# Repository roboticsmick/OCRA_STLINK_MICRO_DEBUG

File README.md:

# ORCA STLINK micro debug tool

Ultra small and low cost STM debugger PCB footprint and programmer PCB. 

## PCB footprint for Fusion 360 

The footprint uses an offset design to ensure you can't connected in reverse. The end pads are through hole pads to act as registration points that the pogo pins align too to keep the profile as small as possible. 

## Programmer PCB boards and Peg

You can find the peg for programming of Aliexpress. This comes disassembled, so you can easily replace the board with the ORCA STLINK micro debug tool PCBs and then connect to your STLINK debugger to program your board.

You will also need to buy a header for your STLINK programmer. This is a 14 pin header, with a 1.27mm pitch. I used one like this:

Alterantively, I've broken our all the STLINK header pins with large 1mm header pins, so you can connect using easily sources 2.54mm header pins, or you can directly solder wires to the pads.

## PCB Design guide instructions

1. Make sure the pads are accessible with the programmer on your PCB design. The component should be near the side of your board, so it can be easily clipped. Ideally make sure no PCB parts obstruct the clip as it's moved into place, as your pogo pins on the programmer could scratch against the components on the board. Always have the peg open all the way when placing the programmer, so the pogo pins do not scratch the PCB.

2. You also need to consider the opposite side of the PCB, as the peg will press against this side of the board to hold the programmer in place. Don't place fragile parts in either areas to prevent damage.

## Programming and debugging

I use a STLINK-V3MINIE. These cost ~$20AU from Digikey to purchase. They incredible value, and make programming with STM32 chips really easy using Zephyr RTOS or Arduino.

## Send some love if you found this helpful

This is completely open source to help out other engineers and tinkers. Enjoy :heart:

If you found it useful though and making bank, feel free to send me some coffees so I can keep making stuff open source!

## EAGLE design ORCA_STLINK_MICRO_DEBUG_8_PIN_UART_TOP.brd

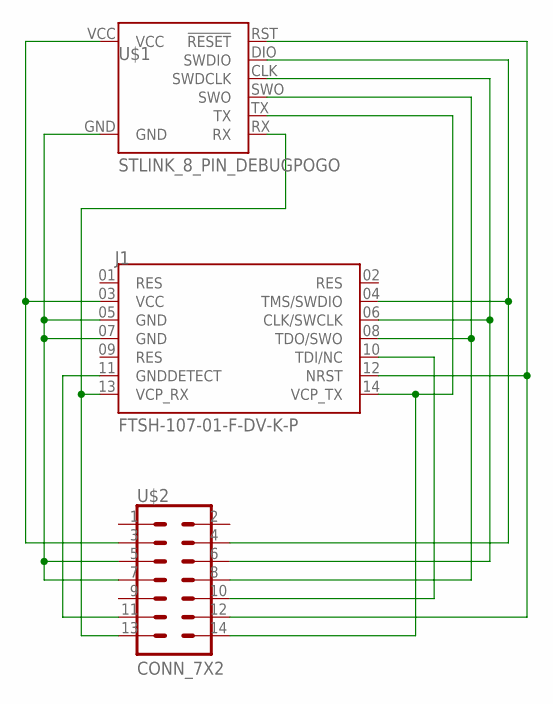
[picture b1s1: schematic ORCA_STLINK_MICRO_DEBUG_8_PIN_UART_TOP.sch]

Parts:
J1: FTSH-107-01-F-DV-K-P; SAMTEC_FTSH-107-01-F-DV-K-P
U$1: STLINK_8_PIN_DEBUGPOGO; STLINK_8_PIN_POGO
U$2: CONN_7X2; 2X07

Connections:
!RST: J1.12 (NRST), U$1.RST (!RESET), U$2.12
CLK: J1.06 (CLK/SWCLK), U$1.CLK (SWDCLK), U$2.6
DIO: J1.04 (TMS/SWDIO), U$1.DIO (SWDIO), U$2.4
GND: J1.05 (GND), J1.07 (GND), U$1.GND, U$2.5, U$2.7
GND_DETECT: J1.11 (GNDDETECT), U$2.11
SWO: J1.08 (TDO/SWO), U$1.SWO, U$2.8
TDI: J1.10 (TDI/NC), U$2.10
VCC: J1.03 (VCC), U$1.VCC, U$2.3
VCP_RX: J1.13 (VCP_RX), U$1.RX, U$2.13
VCP_TX: J1.14 (VCP_TX), U$1.TX, U$2.14

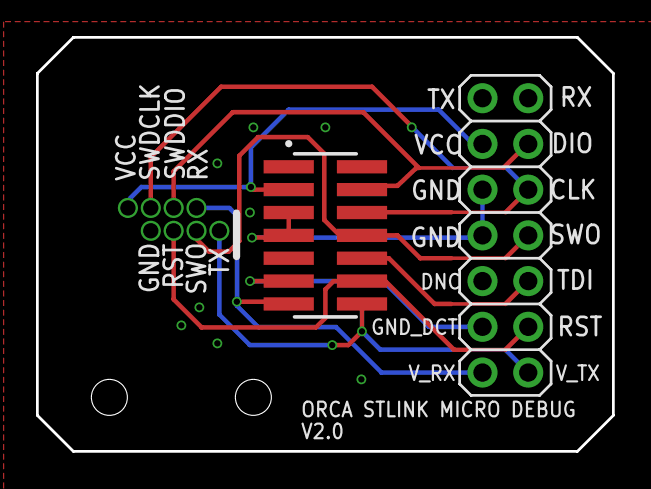
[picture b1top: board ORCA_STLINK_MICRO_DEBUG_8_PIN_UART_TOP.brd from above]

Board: 2 copper layers, 32.0 x 23.0 mm, 3 parts (0 on the bottom side), 10 nets.

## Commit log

2026-02-01 Revise README for ORCA STLINK micro debug tool
    Updated README to reflect new tool name and added details about programming connections and PCB design instructions.
2026-02-01 Enhance README with programming and debugging details
    Added a section on programming and debugging with STLINK-V3MINIE, including a link for support.
